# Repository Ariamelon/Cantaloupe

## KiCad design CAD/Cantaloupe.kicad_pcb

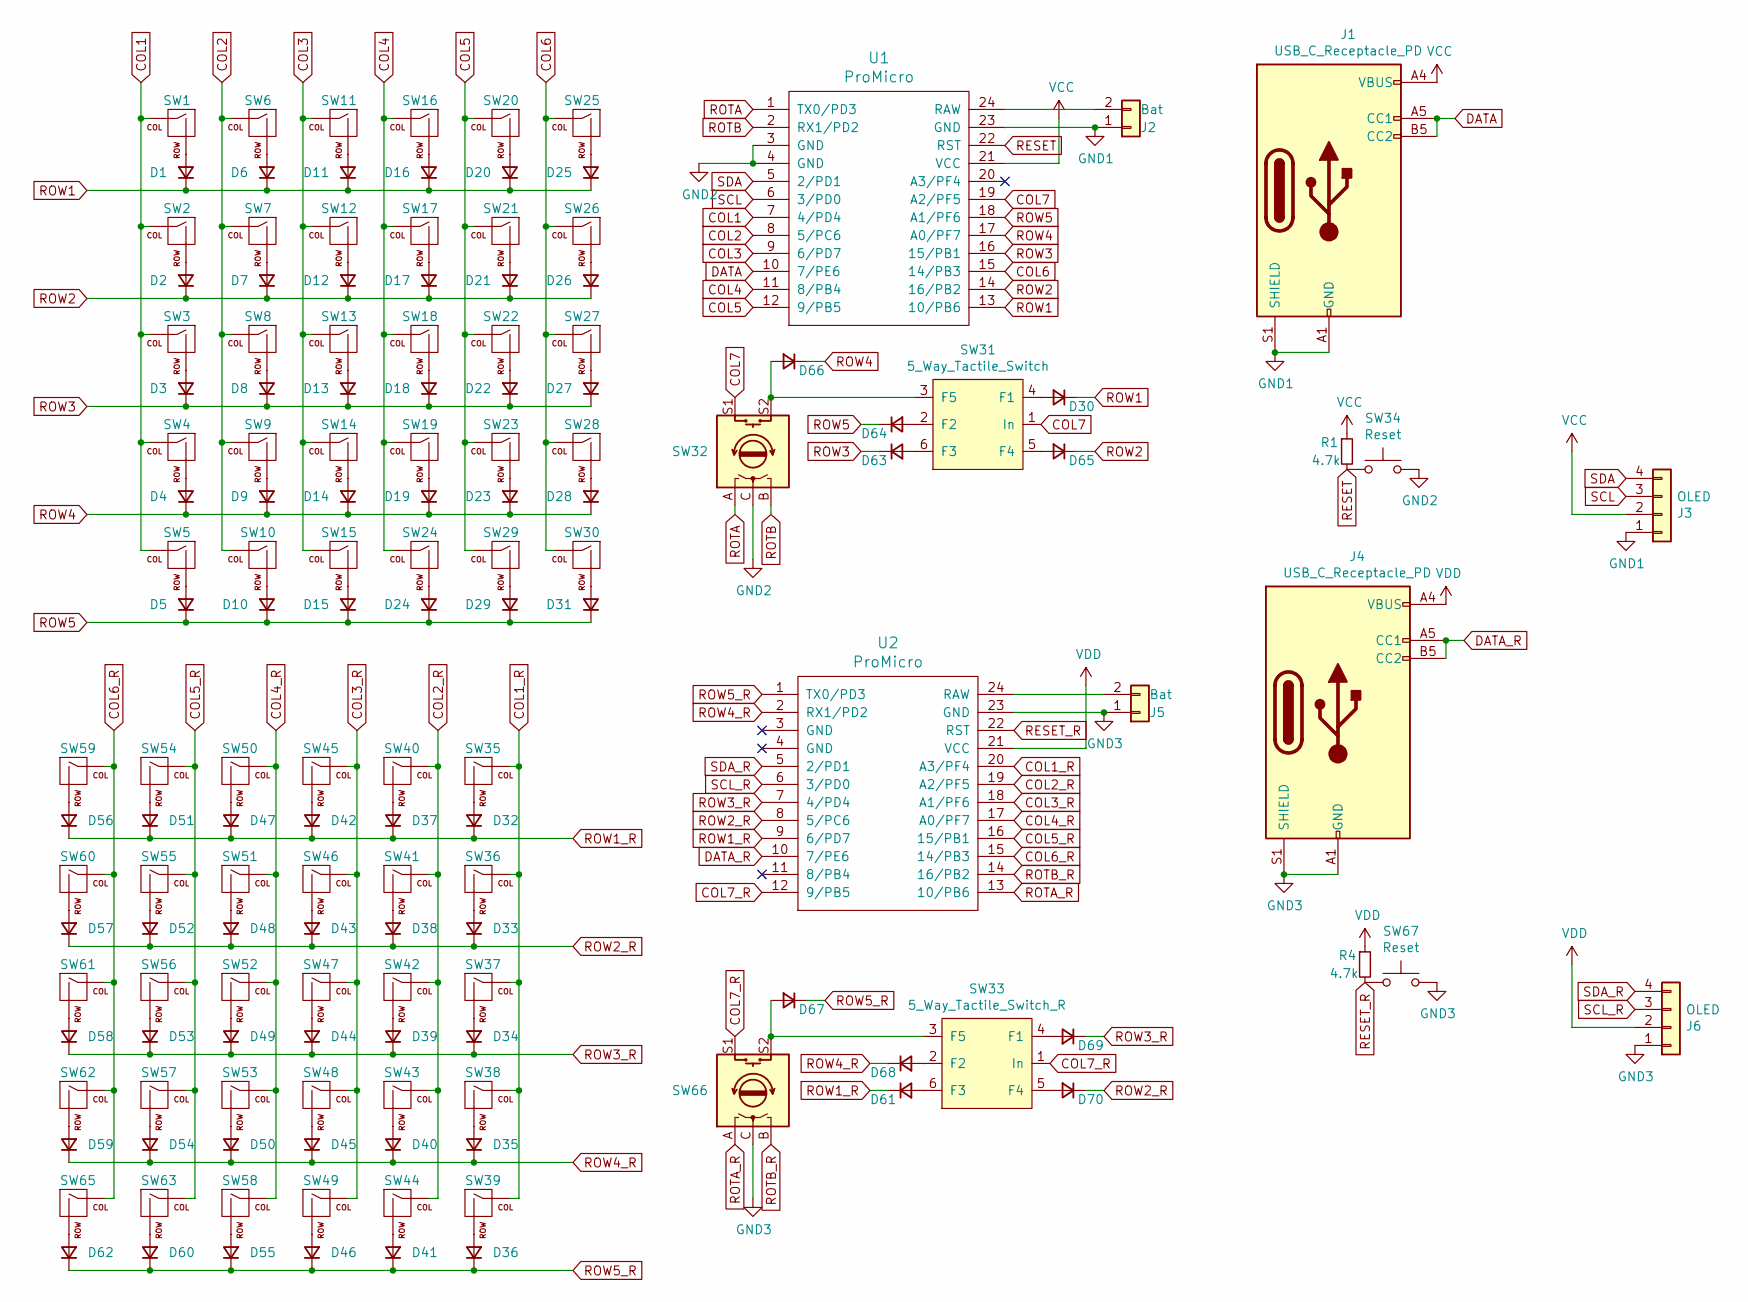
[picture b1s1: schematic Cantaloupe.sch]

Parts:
D1, D2, D3, D4, D5, D6, D7, D8, D9, D10, D11, D12, D13, D14, D15, D16, D17, D18, D19, D20, D21, D22, D23, D24, D25, D26, D27, D28, D29, D30, D31, D32, D33, D34, D35, D36, D37, D38, D39, D40, D41, D42, D43, D44, D45, D46, D47, D48, D49, D50, D51, D52, D53, D54, D55, D56, D57, D58, D59, D60, D61, D62, D63, D64, D65, D66, D67, D68, D69, D70: D; D_SOD-123
J1, J4: USB_C_Receptacle_PD; USB-C-PowerOnly
J2, J5: Bat; Battery_Solder_Points
J3, J6: OLED; PinHeader_1x04_P2.54mm_Vertical_No_Silk
R1, R4: 4.7k; R_0603_1608Metric_Pad1.05x0.95mm_HandSolder
SW1, SW2, SW3, SW4, SW5, SW6, SW7, SW8, SW9, SW10, SW11, SW12, SW13, SW14, SW15, SW16, SW17, SW18, SW19, SW20, SW21, SW22, SW23, SW24, SW25, SW26, SW27, SW28, SW29, SW30, SW35, SW36, SW37, SW38, SW39, SW40, SW41, SW42, SW43, SW44, SW45, SW46, SW47, SW48, SW49, SW50, SW51, SW52, SW53, SW54, SW55, SW56, SW57, SW58, SW59, SW60, SW61, SW62, SW63, SW65: MX; CherryMX_Hotswap_SMK
SW31: 5_Way_Tactile_Switch; 5-way_Tactile_Switch
SW32, SW66: Rotary_Encoder_Switch; RotaryEncoder_Alps_EC11E-Switch_Vertical_H20mm
SW33: 5_Way_Tactile_Switch_R; 5-way_Tactile_Switch
SW34, SW67: Reset; SW_SPST_TL3342
U1, U2: ProMicro; ArduinoProMicro_Blank

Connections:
COL1: SW1.1 (COL), SW2.1 (COL), SW3.1 (COL), SW4.1 (COL), SW5.1 (COL), U1.7 (4/PD4)
COL1_R: SW35.1 (COL), SW36.1 (COL), SW37.1 (COL), SW38.1 (COL), SW39.1 (COL), U2.20 (A3/PF4)
COL2: SW6.1 (COL), SW7.1 (COL), SW8.1 (COL), SW9.1 (COL), SW10.1 (COL), U1.8 (5/PC6)
COL2_R: SW40.1 (COL), SW41.1 (COL), SW42.1 (COL), SW43.1 (COL), SW44.1 (COL), U2.19 (A2/PF5)
COL3: SW11.1 (COL), SW12.1 (COL), SW13.1 (COL), SW14.1 (COL), SW15.1 (COL), U1.9 (6/PD7)
COL3_R: SW45.1 (COL), SW46.1 (COL), SW47.1 (COL), SW48.1 (COL), SW49.1 (COL), U2.18 (A1/PF6)
COL4: SW16.1 (COL), SW17.1 (COL), SW18.1 (COL), SW19.1 (COL), SW24.1 (COL), U1.11 (8/PB4)
COL4_R: SW50.1 (COL), SW51.1 (COL), SW52.1 (COL), SW53.1 (COL), SW58.1 (COL), U2.17 (A0/PF7)
COL5: SW20.1 (COL), SW21.1 (COL), SW22.1 (COL), SW23.1 (COL), SW29.1 (COL), U1.12 (9/PB5)
COL5_R: SW54.1 (COL), SW55.1 (COL), SW56.1 (COL), SW57.1 (COL), SW63.1 (COL), U2.16 (15/PB1)
COL6: SW25.1 (COL), SW26.1 (COL), SW27.1 (COL), SW28.1 (COL), SW30.1 (COL), U1.15 (14/PB3)
COL6_R: SW59.1 (COL), SW60.1 (COL), SW61.1 (COL), SW62.1 (COL), SW65.1 (COL), U2.15 (14/PB3)
COL7: SW31.1 (In), SW32.S1, U1.19 (A2/PF5)
COL7_R: SW33.1 (In), SW66.S1, U2.12 (9/PB5)
DATA: J1.A5 (CC1), J1.B5 (CC2), U1.10 (7/PE6)
DATA_R: J4.A5 (CC1), J4.B5 (CC2), U2.10 (7/PE6)
GND1: J1.A1 (GND), J1.A12 (GND), J1.S1 (SHIELD), J2.1, J3.1, U1.23 (GND)
GND2: SW32.C, SW34.2, U1.3 (GND), U1.4 (GND)
GND3: J4.A1 (GND), J4.A12 (GND), J4.S1 (SHIELD), J5.1, J6.1, SW66.C, SW67.2, U2.23 (GND)
unnamed: D1.2 (A), SW1.2 (ROW)
unnamed: D2.2 (A), SW2.2 (ROW)
unnamed: D3.2 (A), SW3.2 (ROW)
unnamed: D4.2 (A), SW4.2 (ROW)
unnamed: D5.2 (A), SW5.2 (ROW)
unnamed: D6.2 (A), SW6.2 (ROW)
unnamed: D7.2 (A), SW7.2 (ROW)
unnamed: D8.2 (A), SW8.2 (ROW)
unnamed: D9.2 (A), SW9.2 (ROW)
unnamed: D10.2 (A), SW10.2 (ROW)
unnamed: D11.2 (A), SW11.2 (ROW)
unnamed: D12.2 (A), SW12.2 (ROW)
unnamed: D13.2 (A), SW13.2 (ROW)
unnamed: D14.2 (A), SW14.2 (ROW)
unnamed: D15.2 (A), SW15.2 (ROW)
unnamed: D16.2 (A), SW16.2 (ROW)
unnamed: D17.2 (A), SW17.2 (ROW)
unnamed: D18.2 (A), SW18.2 (ROW)
unnamed: D19.2 (A), SW19.2 (ROW)
unnamed: D20.2 (A), SW20.2 (ROW)
unnamed: D21.2 (A), SW21.2 (ROW)
unnamed: D22.2 (A), SW22.2 (ROW)
unnamed: D23.2 (A), SW23.2 (ROW)
unnamed: D24.2 (A), SW24.2 (ROW)
unnamed: D25.2 (A), SW25.2 (ROW)
unnamed: D26.2 (A), SW26.2 (ROW)
unnamed: D27.2 (A), SW27.2 (ROW)
unnamed: D28.2 (A), SW28.2 (ROW)
unnamed: D29.2 (A), SW29.2 (ROW)
unnamed: D30.2 (A), SW31.4 (F1)
unnamed: D31.2 (A), SW30.2 (ROW)
unnamed: D32.2 (A), SW35.2 (ROW)
unnamed: D33.2 (A), SW36.2 (ROW)
unnamed: D34.2 (A), SW37.2 (ROW)
unnamed: D35.2 (A), SW38.2 (ROW)
unnamed: D36.2 (A), SW39.2 (ROW)
unnamed: D37.2 (A), SW40.2 (ROW)
unnamed: D38.2 (A), SW41.2 (ROW)
unnamed: D39.2 (A), SW42.2 (ROW)
unnamed: D40.2 (A), SW43.2 (ROW)
unnamed: D41.2 (A), SW44.2 (ROW)
unnamed: D42.2 (A), SW45.2 (ROW)
unnamed: D43.2 (A), SW46.2 (ROW)
unnamed: D44.2 (A), SW47.2 (ROW)
unnamed: D45.2 (A), SW48.2 (ROW)
unnamed: D46.2 (A), SW49.2 (ROW)
unnamed: D47.2 (A), SW50.2 (ROW)
unnamed: D48.2 (A), SW51.2 (ROW)
unnamed: D49.2 (A), SW52.2 (ROW)
unnamed: D50.2 (A), SW53.2 (ROW)
unnamed: D51.2 (A), SW54.2 (ROW)
unnamed: D52.2 (A), SW55.2 (ROW)
unnamed: D53.2 (A), SW56.2 (ROW)
unnamed: D54.2 (A), SW57.2 (ROW)
unnamed: D55.2 (A), SW58.2 (ROW)
unnamed: D56.2 (A), SW59.2 (ROW)
unnamed: D57.2 (A), SW60.2 (ROW)
unnamed: D58.2 (A), SW61.2 (ROW)
unnamed: D59.2 (A), SW62.2 (ROW)
unnamed: D60.2 (A), SW63.2 (ROW)
unnamed: D61.2 (A), SW33.6 (F3)
unnamed: D62.2 (A), SW65.2 (ROW)
unnamed: D63.2 (A), SW31.6 (F3)
unnamed: D64.2 (A), SW31.2 (F2)
unnamed: D65.2 (A), SW31.5 (F4)
unnamed: D66.2 (A), SW31.3 (F5), SW32.S2
unnamed: D67.2 (A), SW33.3 (F5), SW66.S2
unnamed: D68.2 (A), SW33.2 (F2)
unnamed: D69.2 (A), SW33.4 (F1)
unnamed: D70.2 (A), SW33.5 (F4)
unnamed: J2.2, U1.24 (RAW)
unnamed: J5.2, U2.24 (RAW)
RESET: R1.2, SW34.1, U1.22 (RST)
RESET_R: R4.2, SW67.1, U2.22 (RST)
ROTA: SW32.A, U1.1 (TX0/PD3)
ROTA_R: SW66.A, U2.13 (10/PB6)
ROTB: SW32.B, U1.2 (RX1/PD2)
ROTB_R: SW66.B, U2.14 (16/PB2)
ROW1: D1.1 (K), D6.1 (K), D11.1 (K), D16.1 (K), D20.1 (K), D25.1 (K), D30.1 (K), U1.13 (10/PB6)
ROW1_R: D32.1 (K), D37.1 (K), D42.1 (K), D47.1 (K), D51.1 (K), D56.1 (K), D61.1 (K), U2.9 (6/PD7)
ROW2: D2.1 (K), D7.1 (K), D12.1 (K), D17.1 (K), D21.1 (K), D26.1 (K), D65.1 (K), U1.14 (16/PB2)
ROW2_R: D33.1 (K), D38.1 (K), D43.1 (K), D48.1 (K), D52.1 (K), D57.1 (K), D70.1 (K), U2.8 (5/PC6)
ROW3: D3.1 (K), D8.1 (K), D13.1 (K), D18.1 (K), D22.1 (K), D27.1 (K), D63.1 (K), U1.16 (15/PB1)
ROW3_R: D34.1 (K), D39.1 (K), D44.1 (K), D49.1 (K), D53.1 (K), D58.1 (K), D69.1 (K), U2.7 (4/PD4)
ROW4: D4.1 (K), D9.1 (K), D14.1 (K), D19.1 (K), D23.1 (K), D28.1 (K), D66.1 (K), U1.17 (A0/PF7)
ROW4_R: D35.1 (K), D40.1 (K), D45.1 (K), D50.1 (K), D54.1 (K), D59.1 (K), D68.1 (K), U2.2 (RX1/PD2)
ROW5: D5.1 (K), D10.1 (K), D15.1 (K), D24.1 (K), D29.1 (K), D31.1 (K), D64.1 (K), U1.18 (A1/PF6)
ROW5_R: D36.1 (K), D41.1 (K), D46.1 (K), D55.1 (K), D60.1 (K), D62.1 (K), D67.1 (K), U2.1 (TX0/PD3)
SCL: J3.3, U1.6 (3/PD0)
SCL_R: J6.3, U2.6 (3/PD0)
SDA: J3.4, U1.5 (2/PD1)
SDA_R: J6.4, U2.5 (2/PD1)
VCC: J1.A4 (VBUS), J1.A9 (VBUS), J3.2, R1.1, U1.21 (VCC)
VDD: J4.A4 (VBUS), J4.A9 (VBUS), J6.2, R4.1, U2.21 (VCC)

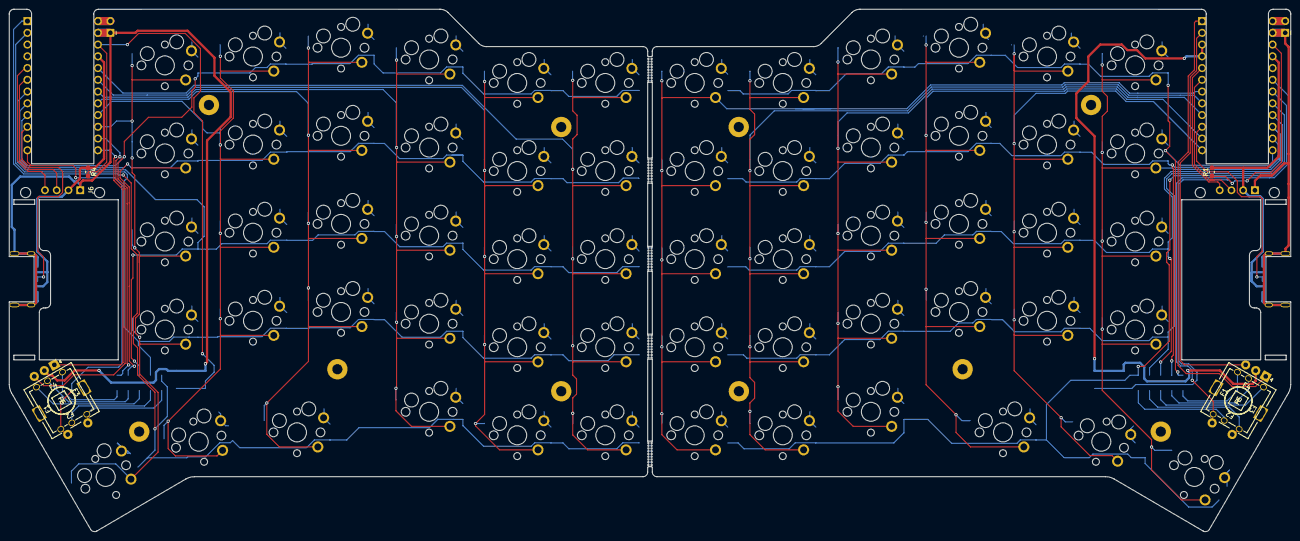
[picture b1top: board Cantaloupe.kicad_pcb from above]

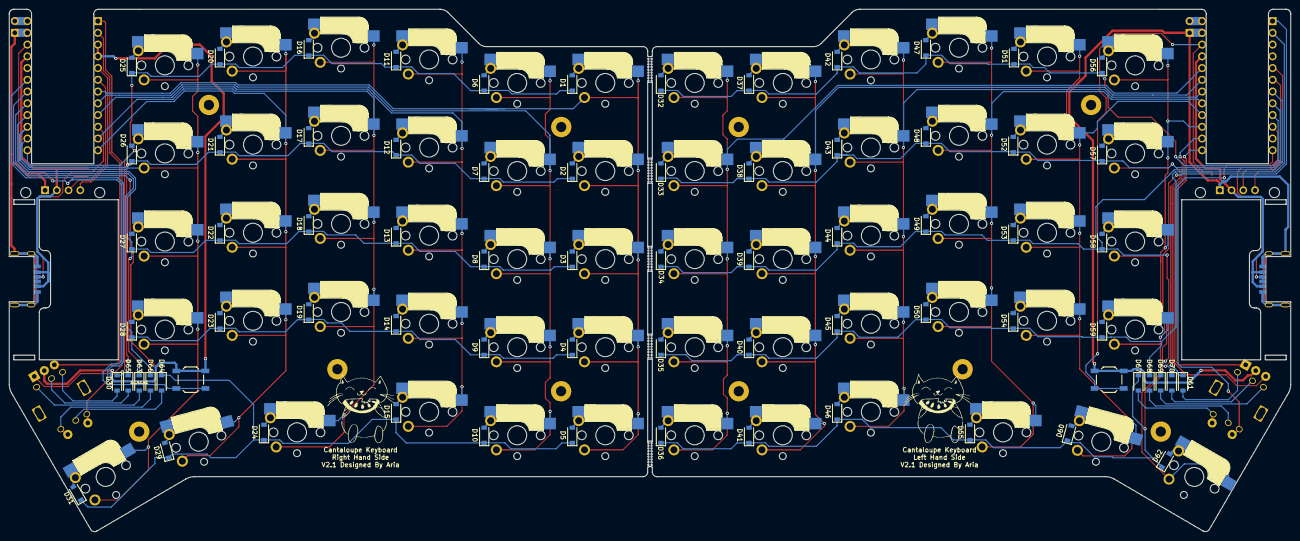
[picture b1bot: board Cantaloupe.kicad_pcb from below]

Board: 2 copper layers, 277.1 x 113.0 mm, 168 parts (76 on the bottom side), 113 nets.

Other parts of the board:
G1, G2: Art; Catmelon
H1, H2, H3, H4, H5, H6, H7, H8, H9, H10: MountingHole; MountingHole_2.2mm_M2_Pad
H11, H11#2, H12, H12#2, H13, H13#2, H14, H14#2, H15, H15#2: Breakaway; Breakaway_Tabs
